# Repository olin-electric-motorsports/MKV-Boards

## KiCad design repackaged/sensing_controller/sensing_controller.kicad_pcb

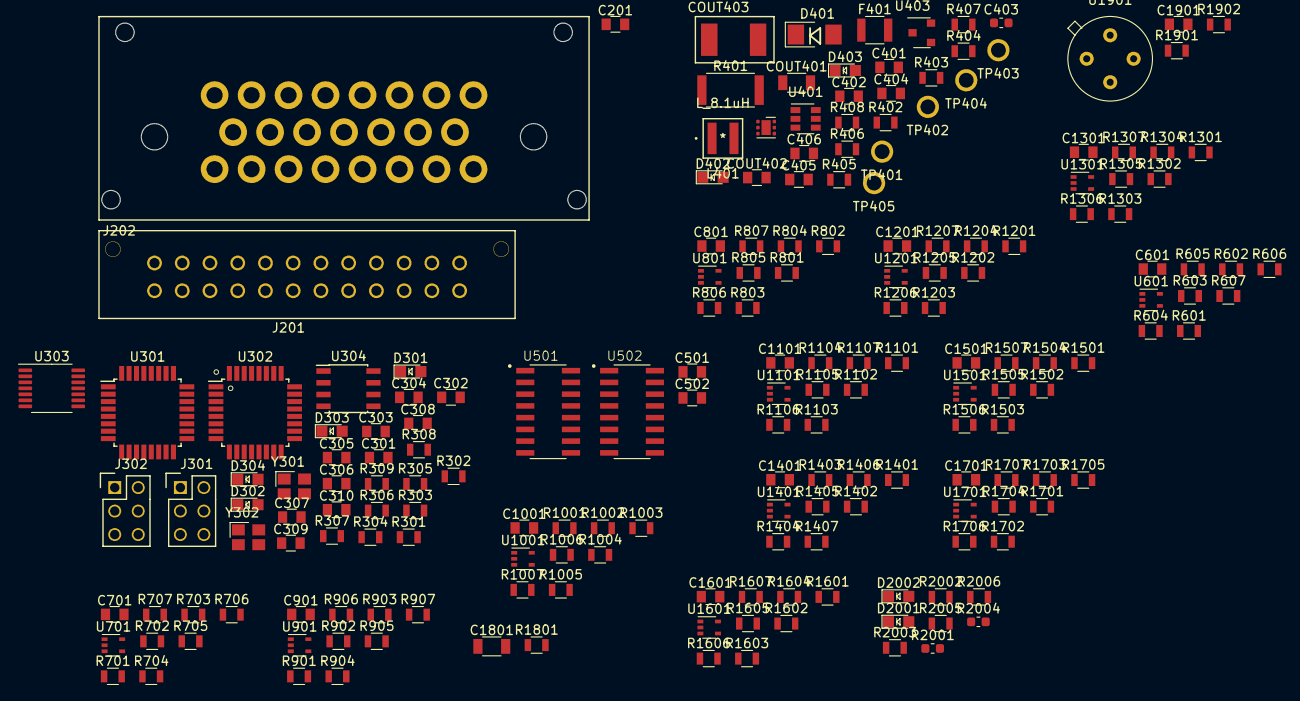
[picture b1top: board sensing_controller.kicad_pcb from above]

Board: 2 copper layers, 190 parts (0 on the bottom side), 118 nets, no tracks yet.

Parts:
C201, C301, C305, C308, C309, C310, C401, C402, C405, C406, C501, C502, C601, C701, C801, C901, C1001, C1101, C1201, C1301, C1401, C1501, C1601, C1701, C1901: C_0.1uF; C_0805_OEM
C302: C_100pF; C_0805_OEM
C303, C304, C306, C307: C_30pF; C_0805_OEM
C403: C_2.2uF; C_0603_1608Metric
C404: C_47uF; C_0805_OEM
C1801: C_22uF; C_1206_OEM
COUT401: C_22uF; C_1206_OEM
COUT402: C_47uF; C_0805_OEM
COUT403: C_33uF; Fuse_1812
D301, D302, D303, D304, D402, D403, D2001, D2002: LED_0805; LED_0805_OEM
D401: D_Zener_18V; DO-214AA
F401: F_500mA_16V; Fuse_1210
J201: MicroFit_24; Molex_Microfit3_Header_02x12_Straight_0444322401_OEM
J202: Ampseal_23_RA; Ampseal_23
J301, J302: CONN_02X03; Pin_Header_Straight_2x03
L401: L_8.1uH
R301, R302, R303, R305, R404, R2003, R2006: R_200; R_0805_OEM
R304: R_100; R_0805_OEM
R306, R307, R308, R406, R2002, R2005: R_10K; R_0805_OEM
R309: R_120_DNP; R_0805_OEM
R401: R_0_2512; R_2512_OEM
R402: R_1K; R_0805_OEM
R403: R_90k; R_0805_OEM
R405: R_15k; R_0805_OEM
R407: R_300K; R_0805_OEM
R408: R_100K; R_0805_OEM
R601, R603, R604, R605, R606, R701, R703, R704, R705, R706, R801, R803, R804, R805, R806, R901, R903, R904, R905, R906, R1001, R1003, R1004, R1005, R1006, R1101, R1103, R1104, R1105, R1106, R1201, R1203, R1204, R1205, R1206, R1301, R1303, R1304, R1305, R1306, R1401, R1403, R1404, R1405, R1406, R1501, R1503, R1504, R1505, R1506, R1601, R1603, R1604, R1605, R1606, R1701, R1703, R1704, R1705, R1706: R_120; R_0805_OEM
R602, R607, R702, R707, R802, R807, R902, R907, R1002, R1007, R1102, R1107, R1202, R1207, R1302, R1307, R1402, R1407, R1502, R1507, R1602, R1607, R1702, R1707: R_4.99K; R_0805_OEM
R1801: R_1K_0.1; R_0805_OEM
R1901, R1902: R_4.7K; R_0805_OEM
R2001, R2004: R_0; R_0603_1608Metric
TP401, TP402, TP403, TP404, TP405: TP; tp_1.6mm
U301: ATmega328P-AU; TQFP-32_7x7mm_P0.8mm
U302: ATMEGA16M1; TQFP-32_7x7mm_Pitch0.8mm
U303: TXB0104; TSSOP-14_4.4x5mm_P0.65mm
U304: MCP2561-E_SN; SOIC-8_3.9x4.9mm_Pitch1.27mm_OEM
U401: TPS560430YF; SOT-23-6_OEM
U402: TPS7A26
U403: LM3480; SOT-23-3_OEM
U501, U502: 74HC4051; SOIC127P600X175-16N
U601, U701, U801, U901, U1001, U1101, U1201, U1301, U1401, U1501, U1601, U1701: MCP6001T-I-LT; SOT-353_SC-70-5
U1901: MLX90621ESF-BAB-000-TU
Y301, Y302: Crystal_SMD; Crystal_SMD_FA238

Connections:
3.3V: C305.1, C308.2, C405.1, C1901.1, J301.2, R306.1, R1901.2, R1902.1, TP405.1, U301.4, U301.6, U301.18, U303.14, U403.1, U1901.3
5V: C201.2, C301.1, C309.1, C310.1, C404.1, C406.1, C501.2, C502.2, J202.1, J202.8, J302.2, R304.1, R307.2, R308.2, R406.2, R407.1, R2001.1, R2004.1, TP404.1, U302.4, U303.1, U304.3, U402.1, U403.2, U501.16, U502.16
7V: R401.1, TP402.1, U402.4, U402.6
12V: F401.2, J202.2, J202.6, J202.17, J202.21, TP401.1
+5V: C601.2, C701.2, C801.2, C901.2, C1001.2, C1101.2, C1201.2, C1301.2, C1401.2, C1501.2, C1601.2, C1701.2, R603.2, R604.2, R703.2, R704.2, R803.2, R804.2, R903.2, R904.2, R1003.2, R1004.2, R1103.2, R1104.2, R1203.2, R1204.2, R1303.2, R1304.2, R1403.2, R1404.2, R1503.2, R1504.2, R1603.2, R1604.2, R1703.2, R1704.2, U601.5, U701.5, U801.5, U901.5, U1001.5, U1101.5, U1201.5, U1301.5, U1401.5, U1501.5, U1601.5, U1701.5
/micros/CAN_RX: U302.7, U304.4
/micros/CAN_TX: U302.6, U304.1
/micros/PM_MISO: J302.1, U302.1, U303.3
/micros/PM_MOSI: J302.4, U302.2, U303.4
/micros/PM_RESET: J302.5, R307.1, U302.31
/micros/PM_SCK: J302.3, U302.12, U303.2
/micros/SM_CS: U301.14, U303.10
/micros/SM_MISO: J301.1, U301.16, U303.12
/micros/SM_MOSI: J301.4, U301.15, U303.11
/micros/SM_RESET: J301.5, R306.2, U301.29
/micros/SM_SCK: J301.3, U301.17, U303.13
/suspension_strain/STRAIN_1A_OUT: R607.2, U501.13, U601.1
/suspension_strain/STRAIN_1B_OUT: R1507.2, U502.13, U1501.1
/suspension_strain/STRAIN_2A_OUT: R707.2, U501.14, U701.1
/suspension_strain/STRAIN_2B_OUT: R1607.2, U502.14, U1601.1
/suspension_strain/STRAIN_3A_OUT: R807.2, U501.15, U801.1
/suspension_strain/STRAIN_3B_OUT: R1707.2, U502.15, U1701.1
/suspension_strain/STRAIN_4A_OUT: R907.2, U501.12, U901.1
/suspension_strain/STRAIN_4B_OUT: R1207.2, U502.12, U1201.1
/suspension_strain/STRAIN_5A_OUT: R1007.2, U501.1, U1001.1
/suspension_strain/STRAIN_5B_OUT: R1307.2, U502.1, U1301.1
/suspension_strain/STRAIN_6A_OUT: R1107.2, U501.5, U1101.1
/suspension_strain/STRAIN_6B_OUT: R1407.2, U502.5, U1401.1
/suspension_strain/strain_1a/WHEATSTONE_OUT_-: R603.1, R605.2, R606.1
/suspension_strain/strain_1b/WHEATSTONE_OUT_-: R1503.1, R1505.2, R1506.1
/suspension_strain/strain_2a/WHEATSTONE_OUT_-: R703.1, R705.2, R706.1
/suspension_strain/strain_2b/WHEATSTONE_OUT_-: R1603.1, R1605.2, R1606.1
/suspension_strain/strain_3a/WHEATSTONE_OUT_-: R803.1, R805.2, R806.1
/suspension_strain/strain_3b/WHEATSTONE_OUT_-: R1703.1, R1705.2, R1706.1
/suspension_strain/strain_4a/WHEATSTONE_OUT_-: R903.1, R905.2, R906.1
/suspension_strain/strain_4b/WHEATSTONE_OUT_-: R1203.1, R1205.2, R1206.1
/suspension_strain/strain_5a/WHEATSTONE_OUT_-: R1003.1, R1005.2, R1006.1
/suspension_strain/strain_5b/WHEATSTONE_OUT_-: R1303.1, R1305.2, R1306.1
/suspension_strain/strain_6a/WHEATSTONE_OUT_-: R1103.1, R1105.2, R1106.1
/suspension_strain/strain_6b/WHEATSTONE_OUT_-: R1403.1, R1405.2, R1406.1
CAN+: J202.4, J202.10, J202.13, J202.19, R309.1, U304.7
CAN-: J202.5, J202.11, J202.14, J202.20, R309.2, U304.6
FRONT_SENSE: D2001.2, R2001.2, R2002.1, U302.28
GND: C201.1, C301.2, C302.2, C303.2, C304.2, C305.2, C306.2, C307.2, C308.1, C309.2, C310.2, C402.1, C403.2, C404.2, C405.2, C406.2, C501.1, C502.1, C601.1, C701.1, C801.1, C901.1, C1001.1, C1101.1, C1201.1, C1301.1, C1401.1, C1501.1, C1601.1, C1701.1, C1801.2, C1901.2, COUT401.1, COUT402.2, COUT403.2, D301.1, D302.1, D303.1, D304.1, D401.2, D402.1, D403.1, J201.13, J201.14, J201.15, J201.16, J201.17, J201.18, J201.19, J201.20, J201.21, J201.22, J201.23, J201.24, J202.3, J202.7, J202.12, J202.16, J202.18, J202.22, J202.23, J301.6, J302.6, R405.2, R408.2, R602.1, R605.1, R702.1, R705.1, R802.1, R805.1, R902.1, R905.1, R1002.1, R1005.1, R1102.1, R1105.1, R1202.1, R1205.1, R1302.1, R1305.1, R1402.1, R1405.1, R1502.1, R1505.1, R1602.1, R1605.1, R1702.1, R1705.1, R2002.2, R2003.2, R2005.2, R2006.2, TP403.1, U301.3, U301.5, U301.21, U302.5, U302.20, U303.7, U304.2, U304.8, U402.5, U403.3, U501.7, U501.8, U502.7, U502.8, U601.2, U701.2, U801.2, U901.2, U1001.2, U1101.2, U1201.2, U1301.2, U1401.2, U1501.2, U1601.2, U1701.2, U1901.4, Y301.2, Y301.4, Y302.2, Y302.4
HALL_EFFECT_SENSE: J202.9, U302.14
LEFT_SENSE: D2002.2, R2004.2, R2005.1, U302.13
LIN_POT_SENSE: J202.15, R1801.1
LIN_POT_SENSE_FILTERED: C1801.1, R1801.2, U302.27
unnamed: C302.1, R304.2, U302.19
unnamed: C303.1, U301.8, Y301.1
unnamed: C304.1, U301.7, Y301.3
unnamed: C306.1, U302.11, Y302.1
unnamed: C307.1, U302.10, Y302.3
unnamed: C401.1, L401.1, U401.6
unnamed: C401.2, U401.1
unnamed: C402.2, C403.1, D401.1, F401.1, R402.1, U401.4, U401.5
unnamed: COUT401.2, COUT402.1, COUT403.1, L401.2, R401.2, R403.1, R404.1
unnamed: D301.2, R301.1
unnamed: D302.2, R302.1
unnamed: D303.2, R303.1
unnamed: D304.2, R305.1
unnamed: D402.2, R402.2
unnamed: D403.2, R404.2
unnamed: D2001.1, R2003.1
unnamed: D2002.1, R2006.1
unnamed: R301.2, U302.8
unnamed: R302.2, U302.9
unnamed: R303.2, U301.12
unnamed: R305.2, U301.13
unnamed: R308.1, U303.8
unnamed: R403.2, R405.1, U401.3
unnamed: R407.2, R408.1, U402.2
unnamed: R601.1, R602.2, U601.3
unnamed: R606.2, R607.1, U601.4
unnamed: R701.1, R702.2, U701.3
unnamed: R706.2, R707.1, U701.4
unnamed: R801.1, R802.2, U801.3
unnamed: R806.2, R807.1, U801.4
unnamed: R901.1, R902.2, U901.3
unnamed: R906.2, R907.1, U901.4
unnamed: R1001.1, R1002.2, U1001.3
unnamed: R1006.2, R1007.1, U1001.4
unnamed: R1101.1, R1102.2, U1101.3
unnamed: R1106.2, R1107.1, U1101.4
unnamed: R1201.1, R1202.2, U1201.3
unnamed: R1206.2, R1207.1, U1201.4
unnamed: R1301.1, R1302.2, U1301.3
unnamed: R1306.2, R1307.1, U1301.4
unnamed: R1401.1, R1402.2, U1401.3
unnamed: R1406.2, R1407.1, U1401.4
unnamed: R1501.1, R1502.2, U1501.3
unnamed: R1506.2, R1507.1, U1501.4
unnamed: R1601.1, R1602.2, U1601.3
unnamed: R1606.2, R1607.1, U1601.4
unnamed: R1701.1, R1702.2, U1701.3
unnamed: R1706.2, R1707.1, U1701.4
SM_SCL: R1901.1, U301.28, U1901.1
SM_SDA: R1902.2, U301.27, U1901.2
STRAIN_1A_+: J201.1, R601.2, R604.1
STRAIN_1B_+: J201.7, R1501.2, R1504.1
STRAIN_2A_+: J201.2, R701.2, R704.1
STRAIN_2B_+: J201.8, R1601.2, R1604.1
STRAIN_3A_+: J201.3, R801.2, R804.1
STRAIN_3B_+: J201.9, R1701.2, R1704.1
STRAIN_4A_+: J201.4, R901.2, R904.1
STRAIN_4B_+: J201.10, R1201.2, R1204.1
STRAIN_5A_+: J201.5, R1001.2, R1004.1
STRAIN_5B_+: J201.11, R1301.2, R1304.1
STRAIN_6A_+: J201.6, R1101.2, R1104.1
STRAIN_6B_+: J201.12, R1401.2, R1404.1
STRAIN_MUX1_OUT: U302.16, U501.3
STRAIN_MUX2_OUT: U302.26, U502.3
STRAIN_S0: U302.29, U501.11, U502.11
STRAIN_S1: U302.17, U501.10, U502.10
STRAIN_S2: U302.23, U501.9, U502.9
Vpg: R406.1, U402.3
nSTRAIN_MUX1_EN: U302.24, U501.6
nSTRAIN_MUX2_EN: U302.30, U502.6

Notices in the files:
parts and their libraries:
Copyright 2016 Accelerated Designs. All rights reserved.
